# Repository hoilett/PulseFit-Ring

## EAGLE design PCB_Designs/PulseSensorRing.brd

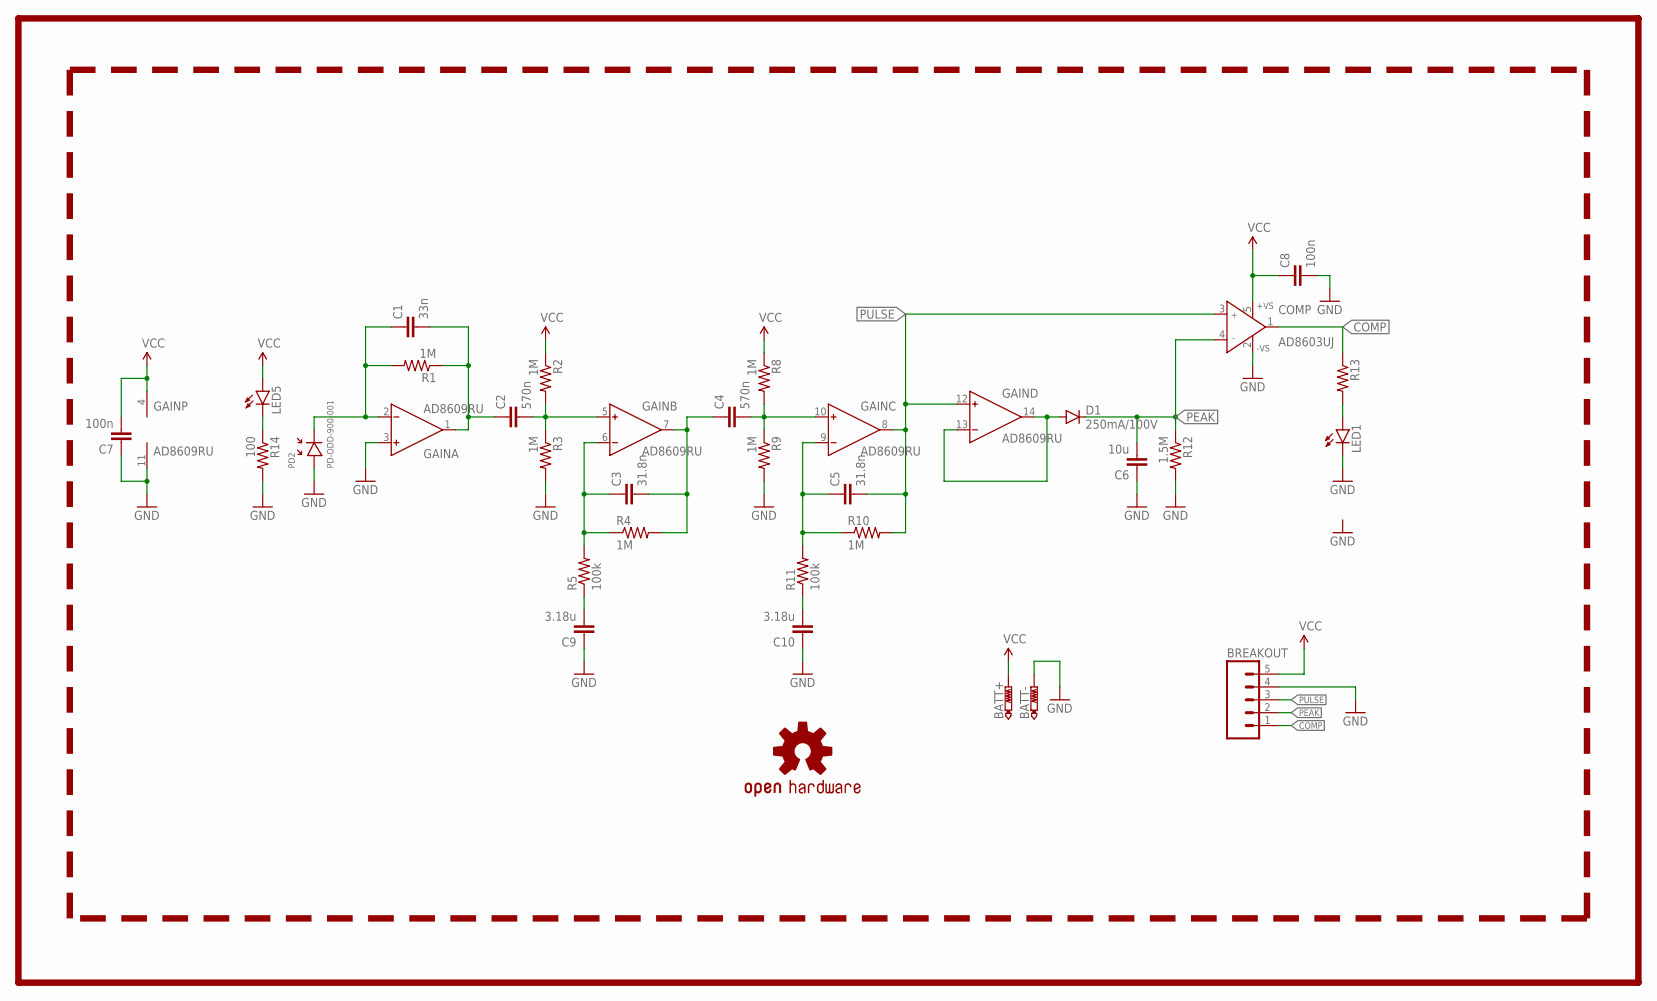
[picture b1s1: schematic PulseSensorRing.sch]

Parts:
BATT: BATT-CONNECT; HOLE
BREAKOUT: M05NO_SILK; 1X05_NO_SILK
C1: 33n; C0402
C2, C4: 570n; C0402
C3, C5: 31.8n; C0402
C6: 10u; C0402
C7, C8: 100n; C0402
C9, C10: 3.18u; C0402
COMP: AD8603UJ; SOT23-5
D1: 250mA/100V; SOD-323
GAIN: AD8609RU; TSSOP14
LED1, LED5: LED0603; LED-0603
LOGO1: OSHW-LOGOS; OSHW-LOGO-S
PD2: PD-ODD-900-001; SMD-PD-01
R1, R2, R3, R4, R8, R9, R10: 1M; R0402
R5, R11: 100k; R0402
R12: 1.5M; R0402
R13: R-US_R0402; R0402
R14: 100; R0402

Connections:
COMP: BREAKOUT.1, COMP.1 (OUT), R13.1
GND: BATT.P$2, BREAKOUT.4, C6.1, C7.1, C8.2, C9.1, C10.1, COMP.2 (-VS), GAIN.3 (IN+), GAIN.11 (V-), LED1.C, PD2.ANODE (+), R3.2, R9.2, R12.2, R14.2
unnamed: C1.1, GAIN.2 (IN-), PD2.CATHODE (-), R1.2
unnamed: C1.2, C2.1, GAIN.1 (OUT), R1.1
unnamed: C4.2, GAIN.10 (IN+), R8.2, R9.1
unnamed: C2.2, GAIN.5 (IN+), R2.2, R3.1
unnamed: C3.1, GAIN.6 (IN-), R4.1, R5.2
unnamed: C3.2, C4.1, GAIN.7 (OUT), R4.2
unnamed: C9.2, R5.1
unnamed: C5.1, GAIN.9 (IN-), R10.1, R11.2
unnamed: LED5.C, R14.1
unnamed: D1.A, GAIN.13 (IN-), GAIN.14 (OUT)
unnamed: C10.2, R11.1
unnamed: LED1.A, R13.2
PEAK: BREAKOUT.2, C6.2, COMP.4 (IN-), D1.C, R12.1
PULSE: BREAKOUT.3, C5.2, COMP.3 (IN+), GAIN.8 (OUT), GAIN.12 (IN+), R10.2
VCC: BATT.P$1, BREAKOUT.5, C7.2, C8.1, COMP.5 (+VS), GAIN.4 (V+), LED5.A, R2.1, R8.1

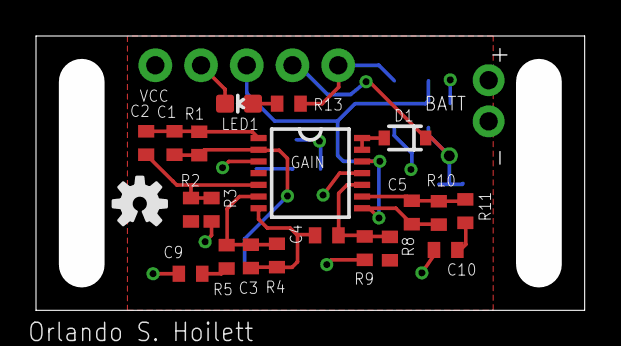
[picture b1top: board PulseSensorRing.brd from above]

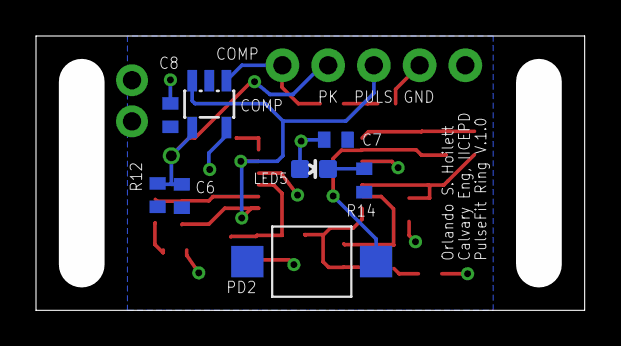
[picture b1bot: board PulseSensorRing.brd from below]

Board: 2 copper layers, 30.5 x 15.2 mm, 31 parts (8 on the bottom side), 17 nets.

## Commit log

2016-08-10 first version of PCB

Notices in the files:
PCB_Designs/PulseSensorRing.brd:
Creative Commons License
parts and their libraries:
SparkFun-DiscreteSemi: Licensing: Creative Commons ShareAlike 4.0 International - https://creativecommons.org/licenses/by-sa/4.0
